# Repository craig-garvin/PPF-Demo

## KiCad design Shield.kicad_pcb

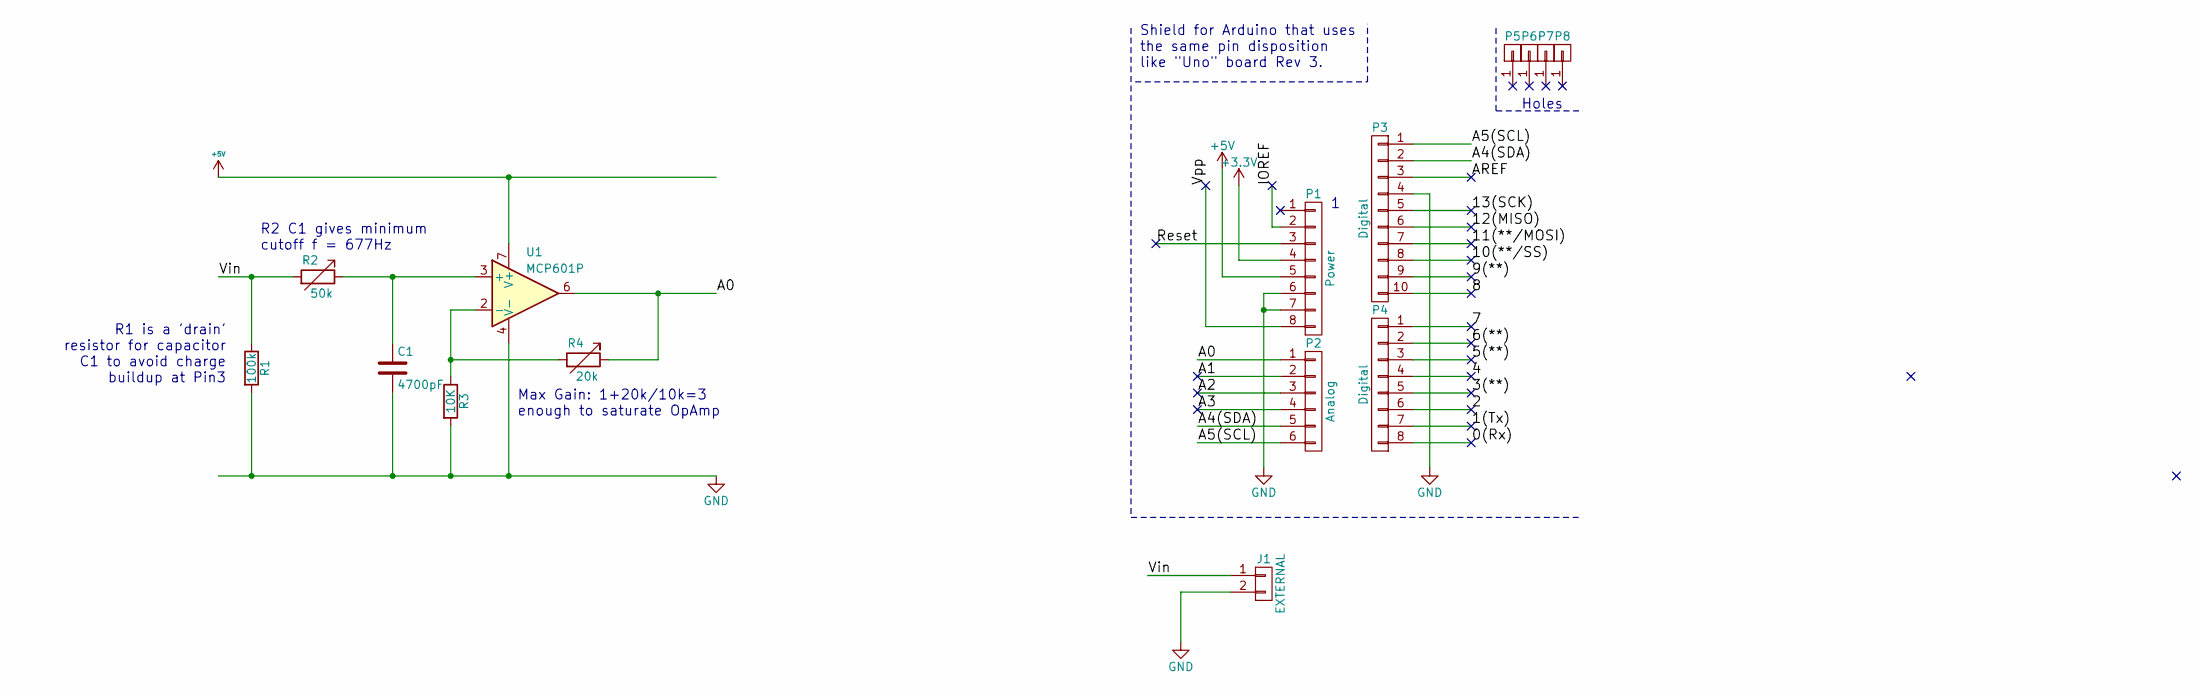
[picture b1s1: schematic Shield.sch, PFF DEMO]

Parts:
C1: 4700pF; CP_Radial_D5.0mm_P2.50mm
J1: EXTERNAL; Socket_Strip_Straight_1x02_Pitch2.54mm
P1: Power; Socket_Strip_Arduino_1x08
P2: Analog; Socket_Strip_Arduino_1x06
P3: Digital; Socket_Strip_Arduino_1x10
P4: Digital; Socket_Strip_Arduino_1x08
P5, P6, P7, P8: CONN_01X01; Arduino_1pin
R1: 100k; R_Axial_DIN0204_L3.6mm_D1.6mm_P5.08mm_Vertical
R2: 50k; Potentiometer_Trimmer_Bourns_3266X
R3: 10K; R_Axial_DIN0204_L3.6mm_D1.6mm_P5.08mm_Vertical
R4: 20k; Potentiometer_Trimmer_Bourns_3266X
U1: MCP601P; DIP-8_W7.62mm

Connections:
+3V3: P1.4
+5V: P1.5, U1.7 (V+)
/0(Rx): P4.8
/1(Tx): P4.7
/2: P4.6
/3(**): P4.5
/4: P4.4
/5(**): P4.3
/6(**): P4.2
/7: P4.1
/8: P3.10
/9(**): P3.9
/10(**/SS): P3.8
/11(**/MOSI): P3.7
/12(MISO): P3.6
/13(SCK): P3.5
/A0: P2.1, R4.1, U1.6
/A1: P2.2
/A2: P2.3
/A3: P2.4
/A4(SDA): P2.5, P3.2
/A5(SCL): P2.6, P3.1
/AREF: P3.3
/IOREF: P1.2
/Reset: P1.3
/Vin: J1.1, R1.1, R2.2
/Vpp: P1.8
GND: C1.2, J1.2, P1.6, P1.7, P3.4, R1.2, R3.2, U1.4 (V-)
unnamed: C1.1, R2.1, U1.3 (+)
unnamed: R3.1, R4.2, U1.2 (-)

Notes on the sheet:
Holes
Shield for Arduino that uses the same pin disposition like "Uno" board Rev 3.
R1 is a 'drain' resistor for capacitor C1 to avoid charge buildup at Pin3
R2 C1 gives minimum cutoff f = 677Hz
Max Gain: 1+20k/10k=3 enough to saturate OpAmp

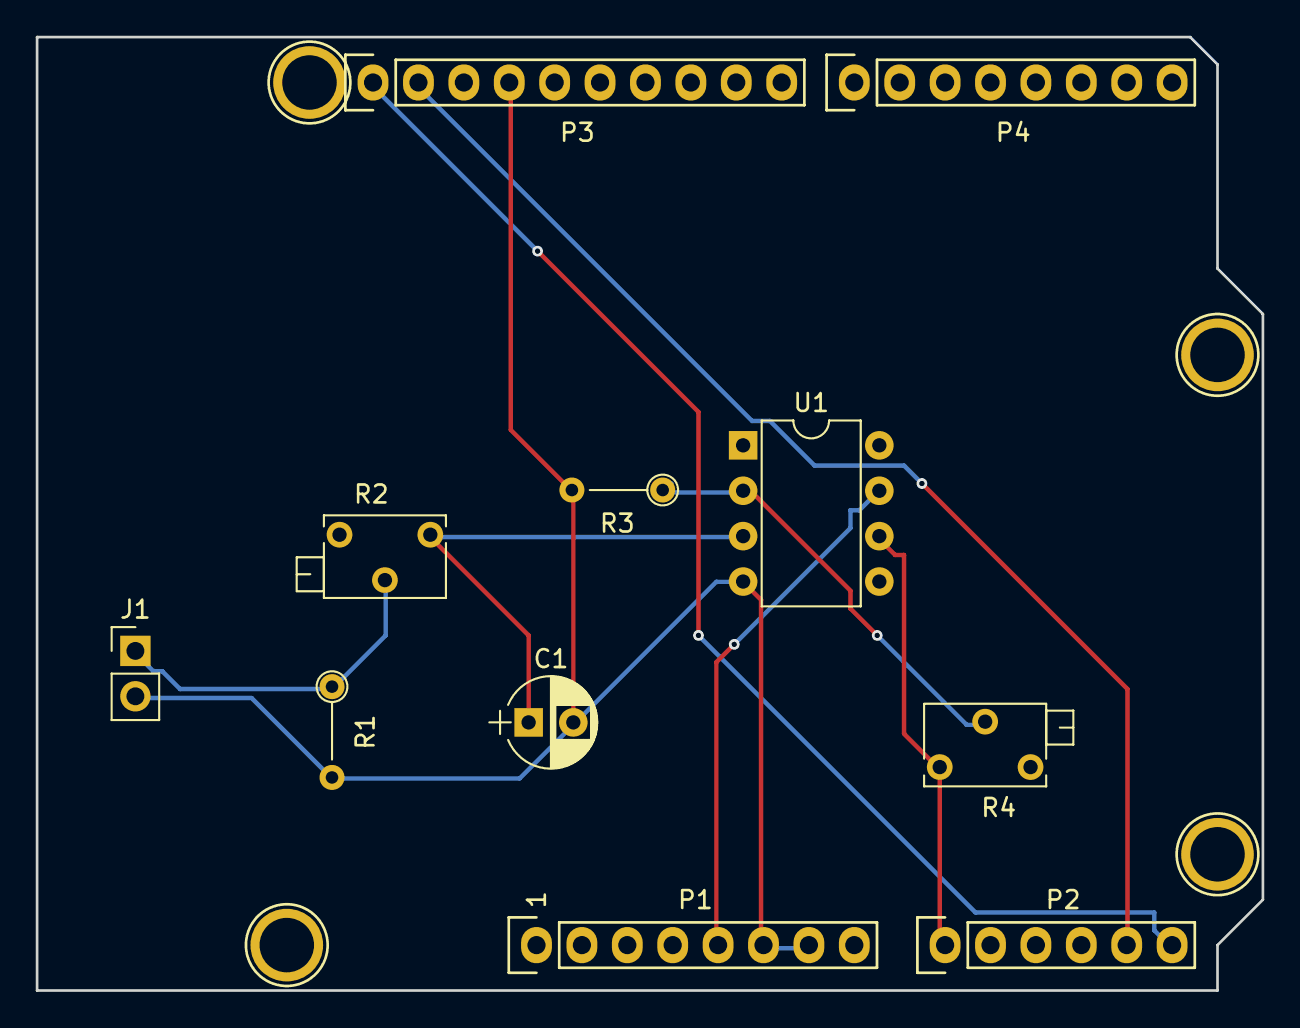
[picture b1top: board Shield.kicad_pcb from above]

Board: 2 copper layers, 68.6 x 53.3 mm, 15 parts (0 on the bottom side), 8 nets.

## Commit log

2017-04-17 Project Submit
